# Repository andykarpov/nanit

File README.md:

# Alternative PCB for NANIT radiation counter.

The original article: https://radiokot.ru/circuit/digital/measure/117/

## Changes to the original schematics:

- Added factory manufactured SMD transformer instead of hand-made coil
- Added LED driver for display backlight

## PCB renders:

## OSHPark project link:

https://oshpark.com/shared_projects/OVV7hNvF

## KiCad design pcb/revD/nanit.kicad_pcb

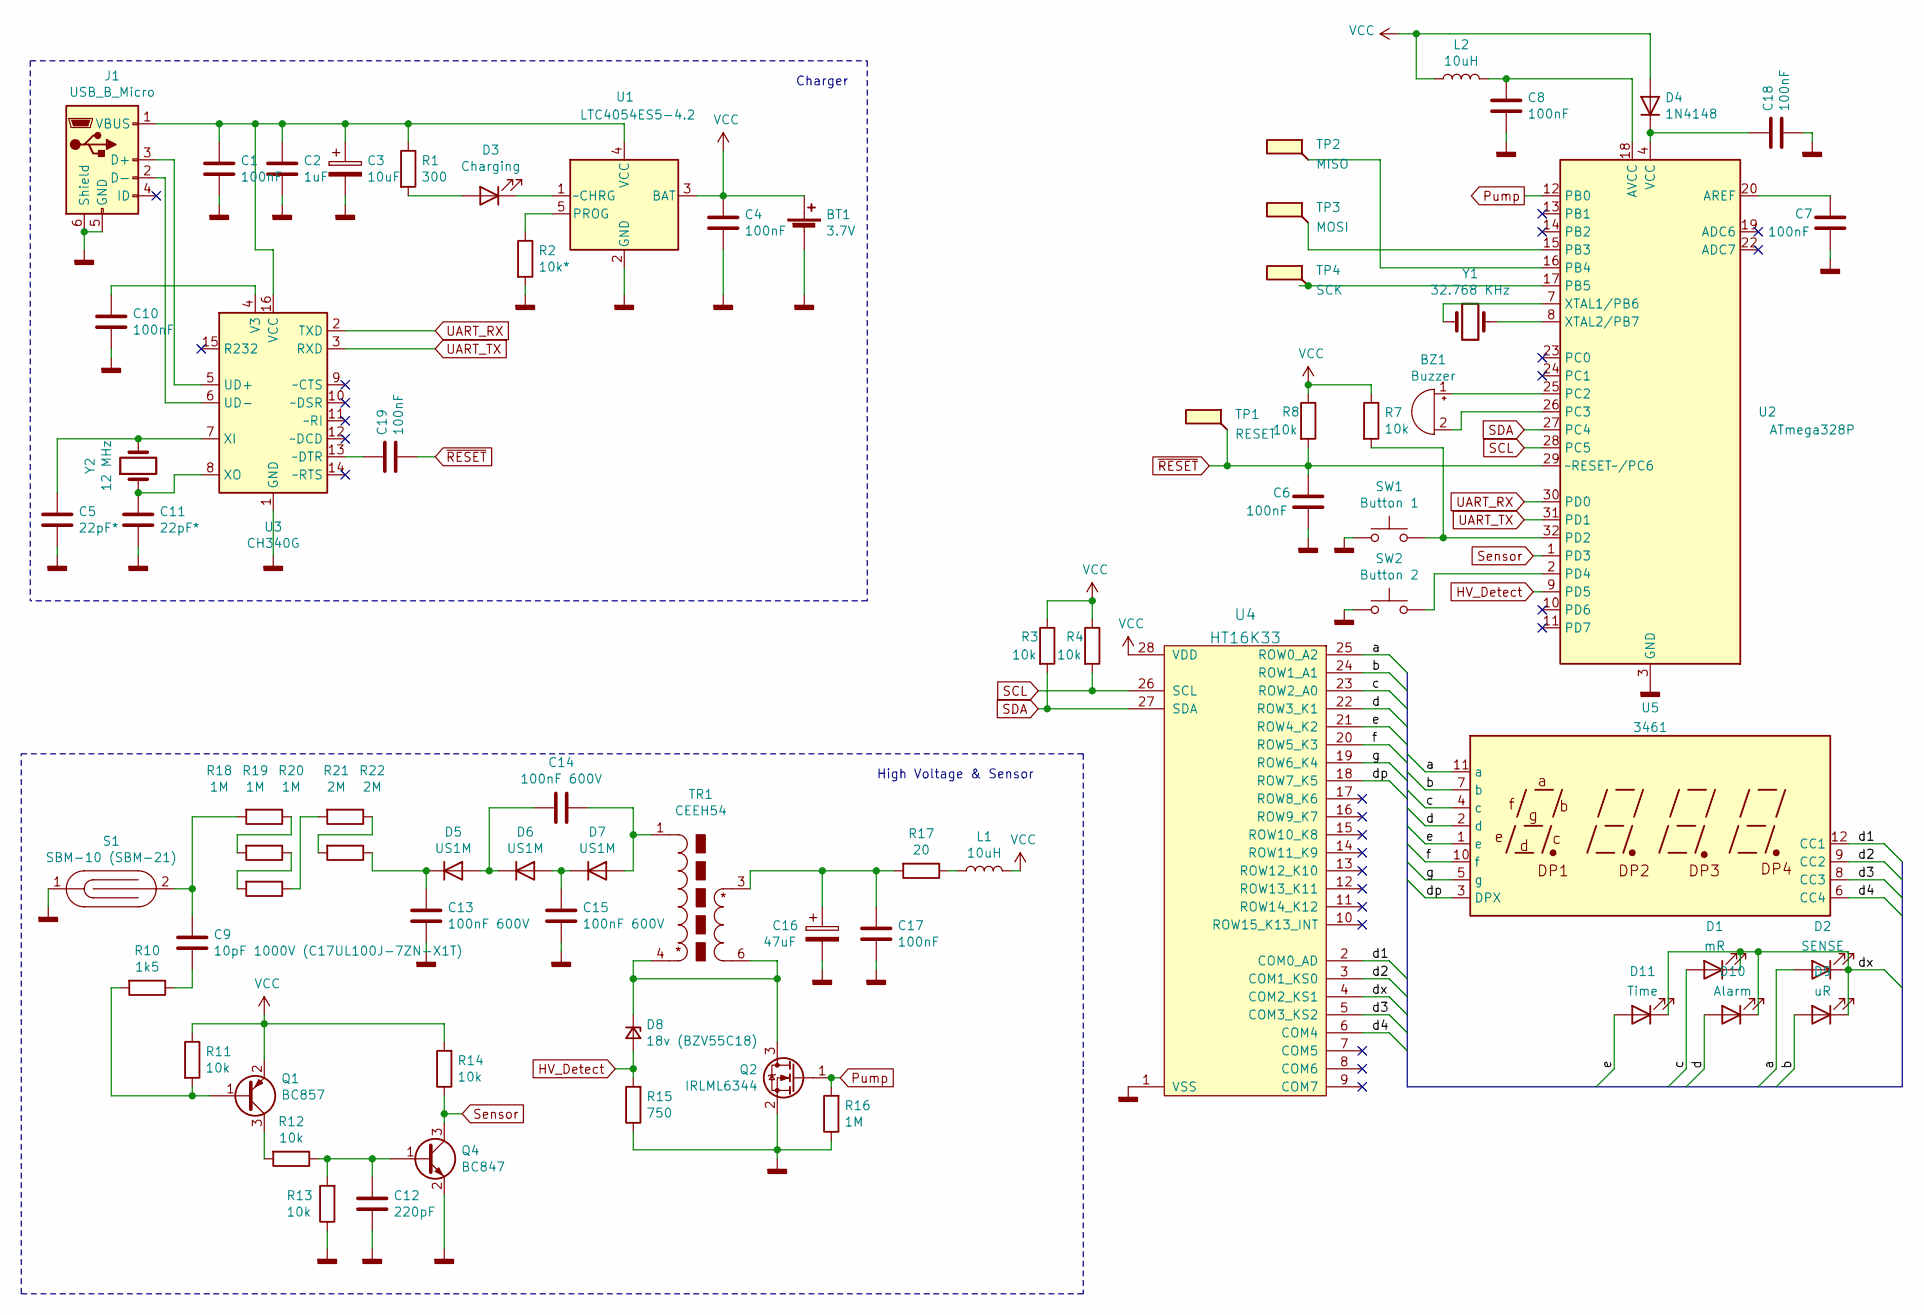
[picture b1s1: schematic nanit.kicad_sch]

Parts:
BT1: 3.7V; PinHeader_1x02_P2.54mm_Vertical
BZ1: Buzzer; PinHeader_1x02_P2.54mm_Vertical
C1, C4, C6, C8, C10, C17, C18, C19: 100nF; C_0805_2012Metric_Pad1.15x1.40mm_HandSolder
C2: 1uF; C_0805_2012Metric_Pad1.15x1.40mm_HandSolder
C3: 10uF; CP_EIA-3216-18_Kemet-A_Pad1.58x1.35mm_HandSolder
C5, C11: 22pF*; C_0805_2012Metric_Pad1.15x1.40mm_HandSolder
C7: 100nF; C_0805_2012Metric_Pad1.18x1.45mm_HandSolder
C9: 10pF 1000V (C17UL100J-7ZN-X1T); C_1206_3216Metric_Pad1.42x1.75mm_HandSolder
C12: 220pF; C_0805_2012Metric_Pad1.15x1.40mm_HandSolder
C13, C14, C15: 100nF 600V; C_1812_4532Metric_Pad1.30x3.40mm_HandSolder
C16: 47uF; CP_EIA-3216-18_Kemet-A_Pad1.58x1.35mm_HandSolder
D1: mR; LED_0805_2012Metric_Pad1.15x1.40mm_HandSolder
D2: SENSE; LED_0805_2012Metric_Pad1.15x1.40mm_HandSolder
D3: Charging; LED_0805_2012Metric_Pad1.15x1.40mm_HandSolder
D4: 1N4148; D_MiniMELF
D5, D6, D7: US1M; D_SMA
D8: 18v (BZV55C18); D_MiniMELF
D9: uR; LED_0805_2012Metric_Pad1.15x1.40mm_HandSolder
D10: Alarm; LED_0805_2012Metric_Pad1.15x1.40mm_HandSolder
D11: Time; LED_0805_2012Metric_Pad1.15x1.40mm_HandSolder
J1: USB_B_Micro; USB_Micro-B_Amphenol_10118194_Horizontal
L1, L2: 10uH; L_0805_2012Metric_Pad1.15x1.40mm_HandSolder
Q1: BC857; SOT-23
Q2: IRLML6344; SOT-23
Q4: BC847; SOT-23
R1: 300; R_0805_2012Metric_Pad1.15x1.40mm_HandSolder
R2: 10k*; R_0805_2012Metric_Pad1.15x1.40mm_HandSolder
R3, R4: 10k; R_0805_2012Metric_Pad1.20x1.40mm_HandSolder
R7, R8, R11, R12, R13, R14: 10k; R_0805_2012Metric_Pad1.15x1.40mm_HandSolder
R10: 1k5; R_0805_2012Metric_Pad1.15x1.40mm_HandSolder
R15: 750; R_0805_2012Metric_Pad1.15x1.40mm_HandSolder
R16, R18, R19, R20: 1M; R_0805_2012Metric_Pad1.15x1.40mm_HandSolder
R17: 20; R_0805_2012Metric_Pad1.15x1.40mm_HandSolder
R21, R22: 2M; R_0805_2012Metric_Pad1.15x1.40mm_HandSolder
S1: SBM-10 (SBM-21); SBM-21
SW1: Button 1; SW_Push_1P1T_NO_6x6mm_H9.5mm
SW2: Button 2; SW_Push_1P1T_NO_6x6mm_H9.5mm
TP1: RESET; TestPoint_Pad_1.5x1.5mm
TP2: MISO; TestPoint_Pad_1.5x1.5mm
TP3: MOSI; TestPoint_Pad_1.5x1.5mm
TP4: SCK; TestPoint_Pad_1.5x1.5mm
TR1: CEEH54
U1: LTC4054ES5-4.2; TSOT-23-5
U2: ATmega328P; TQFP-32_7x7mm_P0.8mm
U3: CH340G; SOIC-16_3.9x9.9mm_P1.27mm
U4: HT16K33; SOIC-28W_7.5x17.9mm_P1.27mm
U5: 3461; 7SEG-3461
Y1: 32.768 KHz; Crystal_C38-LF_D3.0mm_L8.0mm_Horizontal
Y2: 12 MHz; Crystal_HC49-U_Vertical

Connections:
/a: D2.2 (A), U4.25 (ROW0_A2), U5.11 (a)
/b: D9.2 (A), U4.24 (ROW1_A1), U5.7 (b)
/c: D1.2 (A), U4.23 (ROW2_A0), U5.4 (c)
/d: D10.2 (A), U4.22 (ROW3_K1), U5.2 (d)
/d1: U4.2 (COM0_AD), U5.12 (CC1)
/d2: U4.3 (COM1_KS0), U5.9 (CC2)
/d3: U4.5 (COM3_KS2), U5.8 (CC3)
/d4: U4.6 (COM4), U5.6 (CC4)
/dp: U4.18 (ROW7_K5), U5.3 (DPX)
/dx: D1.1 (K), D2.1 (K), D9.1 (K), D10.1 (K), D11.1 (K), U4.4 (COM2_KS1)
/e: D11.2 (A), U4.21 (ROW4_K2), U5.1 (e)
/f: U4.20 (ROW5_K3), U5.10 (f)
/g: U4.19 (ROW6_K4), U5.5 (g)
GNDD: BT1.2 (-), C1.2, C2.2, C3.2, C4.2, C5.2, C6.2, C7.2, C8.2, C10.2, C11.2, C12.2, C13.2, C15.2, C16.2, C17.2, C18.2, J1.5 (GND), J1.6 (Shield), Q2.2 (S), Q4.2 (E), R2.2, R13.1, R15.1, R16.1, S1.1, SW1.1, SW2.1, U1.2 (GND), U2.3 (GND), U2.5 (GND), U2.21 (GND), U3.1 (GND), U4.1 (VSS)
HV_Detect: D8.2 (A), R15.2, U2.9 (PD5)
unnamed: BZ1.1 (-), U2.25 (PC2)
unnamed: BZ1.2 (+), U2.26 (PC3)
unnamed: C1.1, C2.1, C3.1, J1.1 (VBUS), R1.1, U1.4 (VCC), U3.16 (VCC)
unnamed: C5.1, U3.7 (XI), Y2.2
unnamed: C8.1, L2.2, U2.18 (AVCC)
unnamed: C9.1, R18.2, S1.2
unnamed: C9.2, R10.1
unnamed: C10.1, U3.4 (V3)
unnamed: C11.1, U3.8 (XO), Y2.1
unnamed: C12.1, Q4.1 (B), R12.1, R13.2
unnamed: C13.1, D5.1 (K), R22.1
unnamed: C14.1, D5.2 (A), D6.1 (K)
unnamed: C14.2, D7.2 (A), TR1.1
unnamed: C15.1, D6.2 (A), D7.1 (K)
unnamed: C16.1, C17.1, R17.2, TR1.3
unnamed: C18.1, D4.1 (K), U2.4 (VCC), U2.6 (VCC)
unnamed: C19.1, U3.13 (~DTR)
unnamed: D3.1 (K), U1.1 (~CHRG)
unnamed: D3.2 (A), R1.2
unnamed: D8.1 (K), Q2.3 (D), TR1.4, TR1.6
unnamed: J1.2 (D-), U3.6 (UD-)
unnamed: J1.3 (D+), U3.5 (UD+)
unnamed: L1.1, R17.1
unnamed: Q1.1 (B), R10.2, R11.2
unnamed: Q1.3 (C), R12.2
unnamed: R2.1, U1.5 (PROG)
unnamed: R7.2, SW1.2, U2.32 (PD2)
unnamed: R18.1, R19.2
unnamed: R19.1, R20.2
unnamed: R20.1, R21.2
unnamed: R21.1, R22.2
unnamed: SW2.2, U2.2 (PD4)
unnamed: TP2.1, U2.16 (PB4)
unnamed: TP3.1, U2.15 (PB3)
unnamed: TP4.1, U2.17 (PB5)
unnamed: U2.7 (XTAL1/PB6), Y1.1
unnamed: U2.8 (XTAL2/PB7), Y1.2
unnamed: C7.1, U2.20 (AREF)
Pump: Q2.1 (G), R16.2, U2.12 (PB0)
SCL: R4.2, U2.28 (PC5), U4.26 (SCL)
SDA: R3.2, U2.27 (PC4), U4.27 (SDA)
Sensor: Q4.3 (C), R14.1, U2.1 (PD3)
UART_RX: U2.30 (PD0), U3.2 (TXD)
UART_TX: U2.31 (PD1), U3.3 (RXD)
VCC: BT1.1 (+), C4.1, D4.2 (A), L1.2, L2.1, Q1.2 (E), R3.1, R4.1, R7.1, R8.1, R11.1, R14.2, U1.3 (BAT), U4.28 (VDD)
~RESET: C6.1, C19.2, R8.2, TP1.1, U2.29 (~RESET~/PC6)

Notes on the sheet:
Charger
High Voltage & Sensor

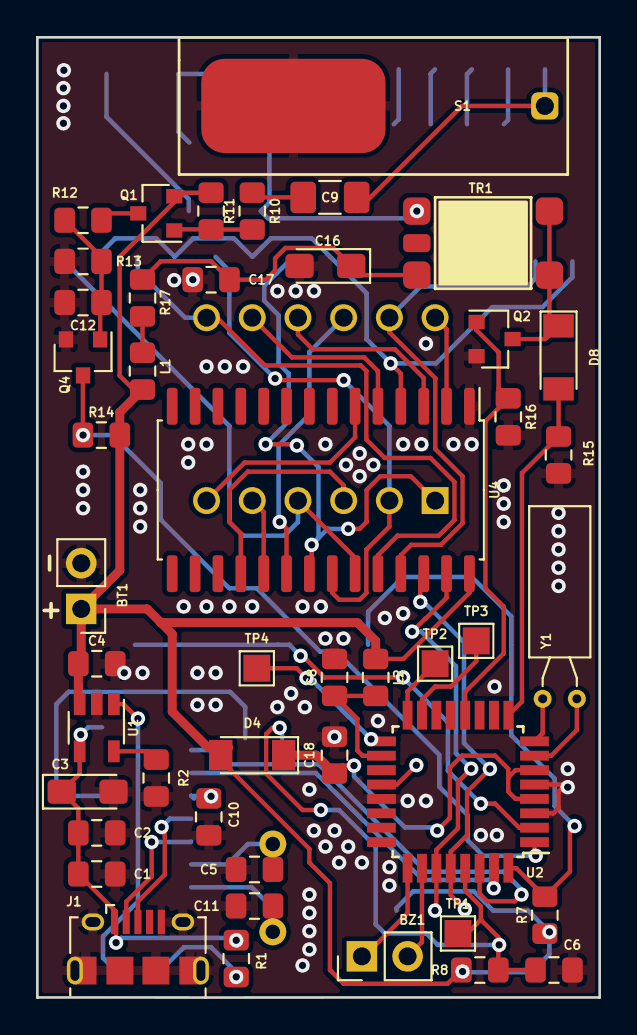
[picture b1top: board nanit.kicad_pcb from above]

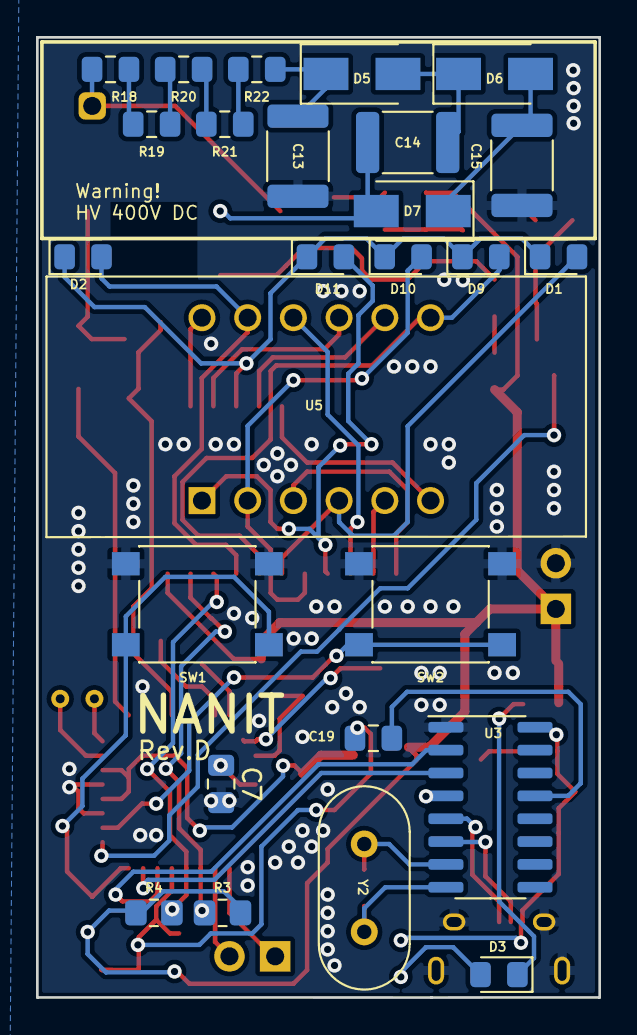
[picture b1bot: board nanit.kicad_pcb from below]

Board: 2 copper layers, 31.2 x 53.3 mm, 72 parts (26 on the bottom side), 61 nets.

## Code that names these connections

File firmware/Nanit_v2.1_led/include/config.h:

#ifndef config_h
#define config_h

// конфигурация пинов
#define PIN_PUMP         8 // PB0

#define PIN_BTN1         2 // PD2
#define PIN_SENSOR       3 // PD3
#define PIN_BTN2         4 // PD4
#define PIN_HV           5 // PD5 

#define PIN_BUZZER1     16 // PC2
#define PIN_BUZZER2     17 // PC3

// тональность звуковых сигналов
#define BEEP_TONE_ALARM 22
#define BEEP_TONE_KEY1  20
#define BEEP_TONE_KEY2  18
#define BEEP_TONE_PWR   14

// тип датчика
#define SENSOR_SBM10     0
#define SENSOR_SBM21     1
#define SENSOR_SBM20	32
#define SENSOR_SI19	    33
#define SENSOR_SBM21_2	34 // 2 счетчика СБМ-21
#define	SENSOR_M_SEL	40 // Выбор через настройки SBM10/SBM21

#ifndef SENSOR_TYPE
#define SENSOR_TYPE SENSOR_SBM21
#endif

// тип батареи
#define BATTERY_LION     0
#define BATTERY_NORMAL   1

#ifndef BATTERY_TYPE
#define BATTERY_TYPE BATTERY_LION
#endif

// тип предупреждения
#define ALARM_DOZE       0
#define ALARM_FON        1

#ifndef ALARM_TYPE
#define ALARM_TYPE ALARM_FON
#endif

// адреса в eeprom для хранения настроек
#define EEPROM_ADDR_BEEP_LEVEL 0
#define EEPROM_ADDR_SLEEP_LEVEL 2
#define EEPROM_ADDR_ALARM_LEVEL 4
#define EEPROM_ADDR_ION 8
#define EEPROM_ADDR_IMPULSE 16
#define EEPROM_ADDR_COUNTER 32
#define EEPROM_ADDR_BRIGHTNESS_LEVEL 128

#endif

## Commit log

2020-02-07 initial version
2020-02-07 Added LED driver for LCD display, gerbers for rev.A
2020-02-07 Refactored a project structure
2020-02-08 Added BOM
2020-02-08 added components placement document
2020-02-08 The original firmware binaries from the article
2020-02-08 latest pcb and schematics
2020-02-08 Added readme
2020-02-08 Fixed readme
2020-02-08 Added PCB rev.A renders
2020-02-08 Added PCB renders
2020-02-08 Firmware binaries and sources from the radiokot.ru/forum
2020-02-08 datasheets
2020-06-02 pcb rev.B
2020-06-02 Latest firmware for m88 and m328
2020-06-02 Docs for rev.B
2020-06-02 latest changes
2020-06-14 Firmware for m88, li, sbm21
2021-07-26 revC
2021-08-20 removed sbm10 firmware
2021-08-21 SSD1306 oled display - initial version
2021-08-21 disabled serial, used SPI for SSD1306
2021-08-21 small fixes
2021-08-23 OLED firmware fixes
2021-08-23 PCB rev.C (OLED version)
2021-08-23 missing docs
2021-08-23 missing pcb files
2021-08-28 revD
2022-05-01 Added firmware for rev.D board
2022-05-07 Fixed beeps, added battery level mode
2022-05-07 Added bootloader for int crystal oscillator
2022-05-07 missing files
2022-07-25 revD fixes - missing AREF capacitor C7
2022-07-29 Fixed Li-Ion discharge level, fixed menu state after awake
2022-07-29 missing file
2022-07-29 Updated firmware
2022-08-22 Fixed config
2022-08-22 updated build
